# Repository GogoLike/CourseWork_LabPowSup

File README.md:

# CourseWork_LabPowSup
Laboratory Power Supply

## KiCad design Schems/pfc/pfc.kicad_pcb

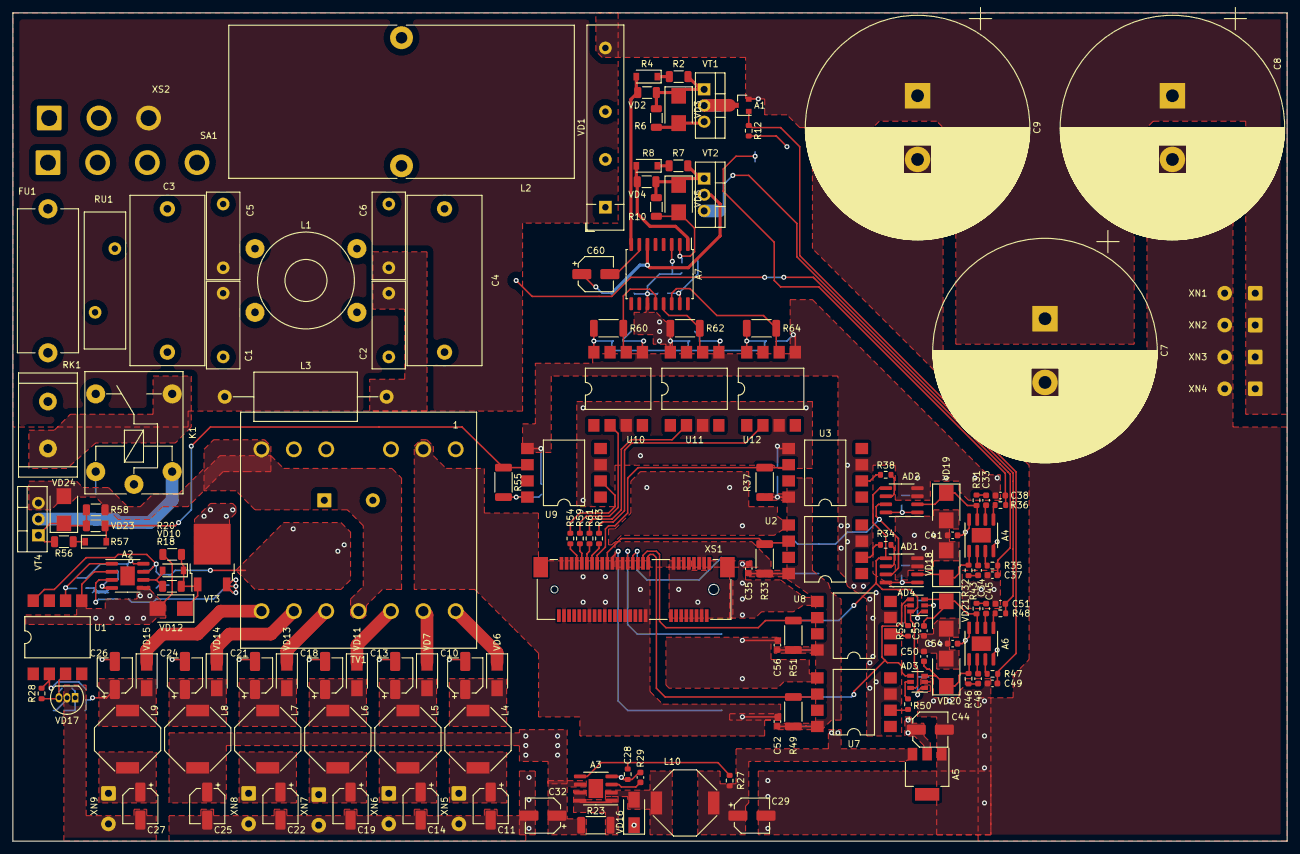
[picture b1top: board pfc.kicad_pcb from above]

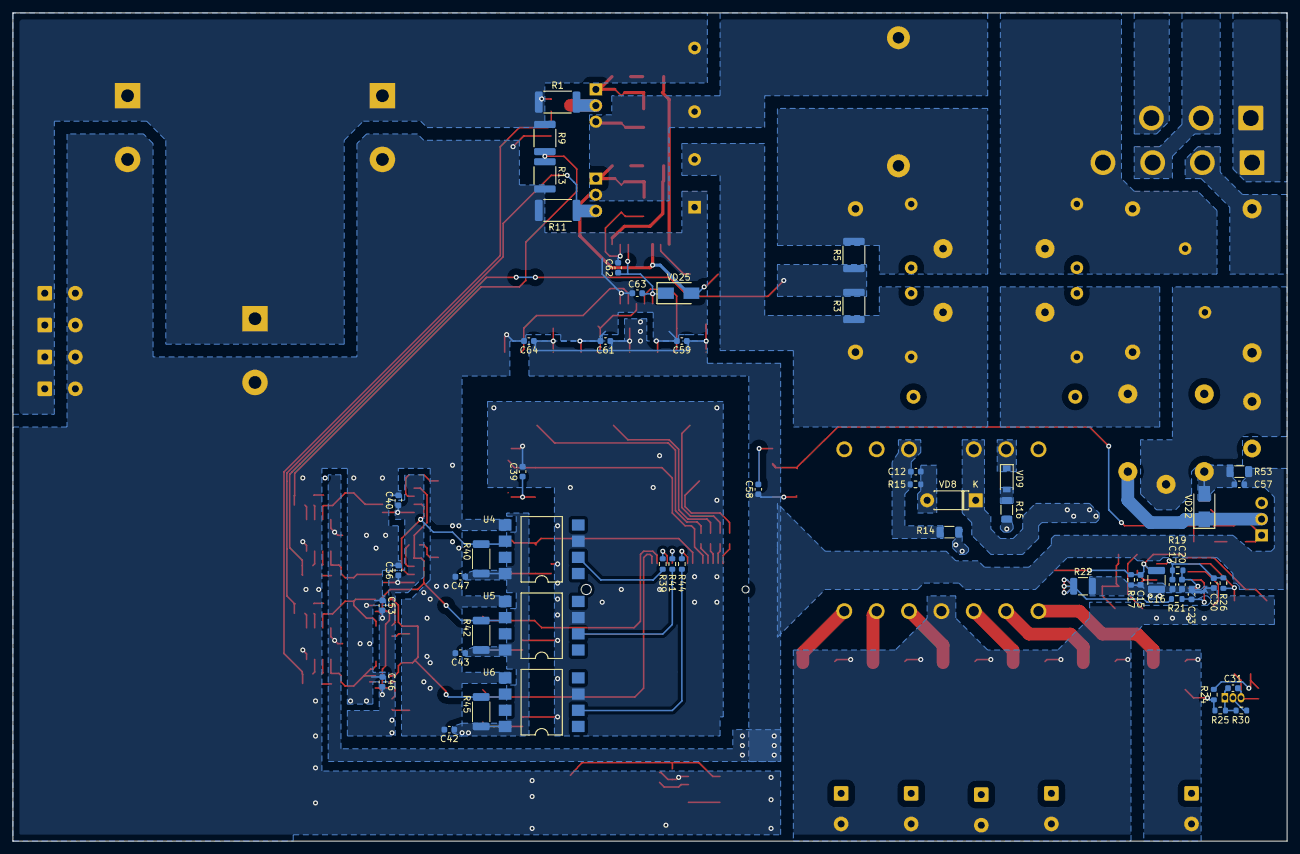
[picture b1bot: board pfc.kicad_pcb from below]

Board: 2 copper layers, 200.0 x 130.0 mm, 207 parts (54 on the bottom side), 118 nets.

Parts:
A1: ZXCT1009F; SOT-23
A2: UC2843; SOIC-8-1EP_3.9x4.9mm_P1.27mm_EP2.29x3mm
A3: MC34063; SOIC-8-1EP_3.9x4.9mm_P1.27mm_EP2.29x3mm
A4, A6: TL103W; SOIC-8-1EP_3.9x4.9mm_P1.27mm_EP2.29x3mm
A5: AMS1117-5; SOT-223
A7: IR2113; SOIC-16W_7.5x10.3mm_P1.27mm
AD1, AD2: MCP3201; SOIC-8_3.9x4.9mm_P1.27mm
AD3, AD4: ADS7886; SOT-23-6
C1, C2, C5, C6: C_CAP; C_Rect_L13.5mm_W5.0mm_P10.00mm_FKS3_FKP3_MKS4
C3, C4: C_CAP; C_Rect_L26.5mm_W11.5mm_P22.50mm_MKS4
C7, C8, C9: 470; CP_Radial_D35.0mm_P10.00mm_SnapIn
C10, C11, C13, C14, C18, C19, C21, C22, C24, C25, C26, C27, C29, C32, C44: 10 25V; CP_Elec_5x5.3
C12: 1.2n; C_0603_1608Metric
C15, C17, C30, C31, C36, C40, C41, C46, C53, C54, C62, C63: 100n; C_0603_1608Metric
C16: 47u; C_1210_3225Metric
C20: 1n; C_0603_1608Metric
C23, C28: 470p; C_0603_1608Metric
C33, C34, C37, C38, C45, C48, C49, C50, C51, C55: C_CAP; C_0603_1608Metric
C35, C39, C42, C43, C47, C52, C56, C58, C59, C61, C64: 15p; C_0603_1608Metric
C57: 1; C_0603_1608Metric
C60: 0.1 25V; CP_Elec_5x5.3
FU1: 20A 250V; Fuseholder_Cylinder-5x20mm_Stelvio-Kontek_PTF78_Horizontal_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
K1: NRP-10-C-12D; Relay_SPDT_Finder_36.11
L1: L_DIEL_DBL_SYN; Transformer_Toroid_Horizontal_D14.0mm_Amidon-T50
L2: L_DIEL; L_Toroid_Vertical_L54.0mm_W23.8mm_P20.10mm_Bourns_5700
L3: L_DIEL; L_Axial_L16.0mm_D7.5mm_P25.40mm_Horizontal_Fastron_XHBCC
L4, L5, L6, L7, L8, L9, L10: 220; L_Bourns-SRU1028_10.0x10.0mm
R1, R11: 0.01 1%; R_2512_6332Metric
R2, R4, R7, R8, R53, R56, R57: R_RES; R_1206_3216Metric
R3, R9: 910k; R_1812_4532Metric
R5, R13: 9.1k; R_1812_4532Metric
R6, R10, R20, R58: 200k; R_1206_3216Metric
R12: 10k 1%; R_0603_1608Metric
R14: 390k; R_1206_3216Metric
R15: 27k; R_0603_1608Metric
R16: 33; R_1206_3216Metric
R17, R25: 15k; R_0603_1608Metric
R18: 22; R_1206_3216Metric
R19: 18k; R_0603_1608Metric
R21, R26, R28: 1k; R_0603_1608Metric
R22: 0.2; R_1210_3225Metric
R23: 0.33; R_2010_5025Metric
R24: 470; R_0603_1608Metric
R27, R29: 4.7k; R_0603_1608Metric
R30: 2k; R_0603_1608Metric
R31, R32, R35, R36, R43, R46, R47, R48: R_RES; R_0603_1608Metric
R33, R37, R40, R42, R45, R49, R51, R55, R60, R62, R64: 100; R_2010_5025Metric
R34, R38, R39, R41, R44, R50, R52, R54, R59, R61, R63: 750; R_0603_1608Metric
RK1: JNR15S221L; R_Radial_Power_L16.1mm_W9.0mm_P7.37mm
RU1: S20K275; RV_Disc_D21.5mm_W6.5mm_P10mm
SA1: 4C 250V 25A; SolderWire-2sqmm_1x04_P7.8mm_D2mm_OD3.9mm
TV1: TV_DIEL_7; Transformer_EPCOS_B66359A1013T_Horizontal
U1, U2, U3, U4, U5, U6, U7, U8: 6N136; SMDIP-8_W11.48mm
U9, U10, U11, U12: 6n136; SMDIP-8_W11.48mm
VD1: KBJ3510; Diode_Bridge_32.0x5.6x17.0mm_P10.0mm_P7.5mm
VD2, VD4, VD23: MBR0540; D_SOD-123
VD3, VD5, VD12, VD24: SMBJ13CA; D_SMB
VD6, VD7, VD11, VD13, VD14, VD15, VD16, VD22, VD25: SK16; D_SMA
VD8: FR107; D_DO-41_SOD81_P7.62mm_Horizontal
VD9, VD10: 1n4148W; D_SOD-123
VD17: TL431; TO-92_Inline
VD18, VD19, VD20, VD21: SMBJ5CA; D_SMB
VT1, VT2: STP34NM60N; TO-220-3_Vertical
VT3: STD3NK80Z; TO-252-2
VT4: VT_NMOS_ENH_GDS; TO-220-3_Vertical
XN1: PWR_OUT0; SolderWire-0.5sqmm_1x02_P4.8mm_D0.9mm_OD2.3mm
XN2: PWR_OUT1; SolderWire-0.5sqmm_1x02_P4.8mm_D0.9mm_OD2.3mm
XN3: PWR_OUT2; SolderWire-0.5sqmm_1x02_P4.8mm_D0.9mm_OD2.3mm
XN4: PWR_OUT3; SolderWire-0.5sqmm_1x02_P4.8mm_D0.9mm_OD2.3mm
XN5: 12V_OUT0; SolderWire-0.5sqmm_1x02_P4.8mm_D0.9mm_OD2.3mm
XN6: 12V_OUT1; SolderWire-0.5sqmm_1x02_P4.8mm_D0.9mm_OD2.3mm
XN7: 12V_OUT2; SolderWire-0.5sqmm_1x02_P4.8mm_D0.9mm_OD2.3mm
XN8: 12V_OUT3; SolderWire-0.5sqmm_1x02_P4.8mm_D0.9mm_OD2.3mm
XN9: 5V_OUT; SolderWire-0.5sqmm_1x02_P4.8mm_D0.9mm_OD2.3mm
XS1: PCIe_mini; BUS_PCI_Express_Mini_Half
XS2: PWR_IN; SolderWire-2sqmm_1x03_P7.8mm_D2mm_OD3.9mm

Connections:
0: C26.2, C27.2, C35.2, C39.2, C52.2, C56.2, R30.2, TV1.2, U2.5, U3.5, U4.3, U5.3, U6.3, U7.5, U8.5, U9.3, U10.3, U11.3, U12.3, VD17.2, XN9.2, XS1.4, XS1.9, XS1.15, XS1.18, XS1.21, XS1.26, XS1.27, XS1.29, XS1.34, XS1.35, XS1.40, XS1.50
+5V: C27.1, C35.1, C39.1, C52.1, C56.1, L9.2, R33.2, R37.2, R49.2, R51.2, U2.8, U3.8, U7.8, U8.8, XN9.1, XS1.3, XS1.5
+6V: A5.3, C29.1, C42.1, C43.1, C47.1, L10.2, R27.1, R40.2, R42.2, R45.2, U4.8, U5.8, U6.8
+12V: A3.6, A4.8, A6.8, A7.3, A7.11, C25.1, C32.1, C41.1, C54.1, C57.1, C58.1, C59.1, C61.1, C62.1, C63.2, C64.1, L8.2, R23.2, R53.1, R55.2, R60.2, R62.2, R64.2, U9.8, U10.8, U11.8, U12.8, VD25.1
+400V: A1.2, C7.1, C8.1, C9.1, C12.1, R1.1, R9.1, R14.1, R15.1, TV1.3, VD1.1, XN1.1, XN2.1, XN3.1, XN4.1
-400V: A2.2, A2.5, A3.4, A4.4, A5.1, A6.4, A7.2, A7.15, AD1.3, AD1.4, AD2.3, AD2.4, AD3.2, AD4.2, C7.2, C8.2, C9.2, C10.2, C11.2, C13.2, C14.2, C15.2, C16.2, C17.2, C18.2, C19.2, C20.2, C21.2, C22.2, C23.2, C24.2, C25.2, C28.2, C29.2, C30.2, C32.2, C36.2, C37.1, C38.2, C40.2, C41.2, C42.2, C43.2, C44.2, C46.1, C47.2, C49.1, C50.2, C51.2, C53.1, C54.2, C55.2, C58.2, C59.2, C61.2, C62.2, C63.1, C64.2, R10.2, R11.2, R12.2, R13.2, R17.2, R20.2, R22.2, R29.2, R58.2, TV1.7, TV1.11, U1.5, U2.3, U3.3, U4.5, U5.5, U6.5, U7.3, U8.3, U9.5, U10.5, U11.5, U12.5, VD1.4, VD5.2, VD12.2, VD16.1, VD18.2, VD19.2, VD20.2, VD21.2, VD24.2, VT4.3, XN1.2, XN2.2, XN3.2, XN4.2, XN5.2, XN6.2, XN7.2, XN8.2
CLK: R39.1, XS1.23
GND: C1.2, C5.1, L3.1, XS2.3
HI: R59.1, XS1.43
HO: A7.8, R4.1, VD2.2
HS: A7.6, C60.1, L2.2, R6.2, VD1.3, VD3.2, VD25.2, VT1.3, VT2.2
IdwD: R51.1, U8.6, XS1.19
IdwS: C51.1, R11.1, R48.2, VT2.3
IupD: R49.1, U7.6, XS1.17
IupS: A1.1, C49.2, R12.1, R47.2
LI: R63.1, XS1.39
LO: A7.1, R8.1, VD4.2
unnamed: A1.3, R1.2, VT1.2
unnamed: A2.1, R26.2, U1.6
unnamed: A2.3, C23.1, R21.1
unnamed: A2.4, C20.1, R19.2
unnamed: A2.6, R18.1, VD10.2
unnamed: A2.7, C15.1, C16.1, R14.2, R16.1, R17.1, U1.8
unnamed: A2.8, C17.1, C30.1, R19.1, R26.1
unnamed: A3.1, A3.7, A3.8, R23.1
unnamed: A3.2, L10.1, VD16.2
unnamed: A3.3, C28.1
unnamed: A3.5, R27.2, R29.1
unnamed: A4.1, AD1.2, R32.1, VD18.1
unnamed: A4.2, C34.2
unnamed: A4.3, R35.1
unnamed: A4.5, R36.1
unnamed: A4.6, C33.2
unnamed: A4.7, AD2.2, R31.1, VD19.1
unnamed: A5.2, AD1.1, AD1.8, AD2.1, AD2.8, AD3.1, AD4.1, C36.1, C40.1, C44.1, C46.2, C53.2
unnamed: A6.1, AD3.3, C50.1, R46.1, VD20.1
unnamed: A6.2, C48.2
unnamed: A6.3, R47.1
unnamed: A6.5, R48.1
unnamed: A6.6, C45.2
unnamed: A6.7, AD4.3, C55.1, R43.1, VD21.1
unnamed: A7.7, C60.2
unnamed: A7.12, R60.1, U10.6
unnamed: A7.13, R62.1, U11.6
unnamed: A7.14, R64.1, U12.6
unnamed: AD1.5, AD2.5, AD3.6, AD4.6, R42.1, U5.6
unnamed: AD1.6, R34.1
unnamed: AD1.7, AD2.7, R40.1, U4.6
unnamed: AD2.6, R38.1
unnamed: AD3.4, AD4.4, R45.1, U6.6
unnamed: AD3.5, R50.1
unnamed: AD4.5, R52.1
unnamed: C1.1, C3.1, K1.5, L1.1, RK1.2
unnamed: C2.1, C4.1, L1.2, R3.1, VD1.2
unnamed: C2.2, C6.1, L3.2
unnamed: C3.2, C5.2, L1.3, RU1.1, SA1.4
unnamed: C4.2, C6.2, L1.4, L2.1, R5.2
unnamed: C10.1, L4.1, VD6.2
unnamed: C11.1, L4.2, XN5.1
unnamed: C12.2, R15.2, VD8.2
unnamed: C13.1, L5.1, VD7.2
unnamed: C14.1, L5.2, XN6.1
unnamed: C18.1, L6.1, VD11.2
unnamed: C19.1, L6.2, XN7.1
unnamed: C21.1, L7.1, VD13.2
unnamed: C22.1, L7.2, XN8.1
unnamed: C24.1, L8.1, VD14.2
unnamed: C26.1, L9.1, R24.1, R25.1, VD15.2
unnamed: C31.1, R28.2, U1.3, VD17.3
unnamed: C31.2, R25.2, R30.1, VD17.1
unnamed: C33.1, R31.2
unnamed: C34.1, R32.2
unnamed: C45.1, R43.2
unnamed: C48.1, R46.2
unnamed: FU1.1, SA1.2
unnamed: FU1.2, K1.4, RK1.1, RU1.2
unnamed: R2.1, VD2.1
unnamed: R2.2, R4.2, R6.1, VD3.1, VT1.1
unnamed: R7.1, VD4.1
unnamed: R7.2, R8.2, R10.1, VD5.1, VT2.1
unnamed: R16.2, VD9.2
unnamed: R18.2, R20.1, VD10.1, VD12.1, VT3.1
unnamed: R21.2, R22.1, VT3.3
unnamed: R24.2, R28.1, U1.2
unnamed: R34.2, U2.2
unnamed: R38.2, U3.2
unnamed: R39.2, U4.2
unnamed: R41.2, U5.2
unnamed: R44.2, U6.2
unnamed: R50.2, U7.2
unnamed: R52.2, U8.2
unnamed: R54.2, U9.2
unnamed: R55.1, R57.1, U9.6, VD23.2
unnamed: R56.1, VD23.1
unnamed: R56.2, R57.2, R58.1, VD24.1, VT4.1
unnamed: R59.2, U10.2
unnamed: R61.2, U11.2
unnamed: R63.2, U12.2
unnamed: SA1.1, XS2.1
unnamed: SA1.3, XS2.2
unnamed: TV1.5, VD8.1, VT3.2
unnamed: TV1.6, VD9.1
unnamed: TV1.8, VD15.1
unnamed: TV1.9, VD14.1
unnamed: TV1.10, VD13.1
unnamed: TV1.12, VD11.1
unnamed: TV1.13, VD7.1
unnamed: TV1.14, VD6.1
Relay: R54.1, XS1.45
RelayCtrl+: C57.2, K1.2, R53.2, VD22.2
RelayCtrl-: K1.1, VD22.1, VT4.2
SCLK: R44.1, XS1.31
SD: R61.1, XS1.41
UinD: R33.1, U2.6, XS1.33
UinS: C37.2, R3.2, R5.1, R35.2
UoutD: R37.1, U3.6, XS1.37
UoutS: C38.1, R9.2, R13.1, R36.2
~CS: R41.1, XS1.25

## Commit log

2021-10-31 Adding all files
    Добавил файлы, лежащие локально на ноутбуке.
2021-10-31 Edit .gitignore and edit Полумост.cir
2021-10-31 Add Объединение обмоток
2021-11-21 Начал расчёт обратноходовой дежурки
2021-12-04 Добавил книги
2021-12-04 Сложил книги в папку
2021-12-04 Переложил рпз. Отредактировал gitignore под файлы микрокапа.
2021-12-04 Тщетные попытки заставить обратноходовик работать.
2021-12-15 Добавил книги по микрокапу от Загидуллина
2022-02-03 Много изменений
2022-03-05 Дежурное питание заново
2022-03-05 Сделал идеальный трансформатор на нужное количество портов
    Исследовал разные трансформаторы в простейшей схеме.
    Пришёл к выводу, что хватит и идеального.
    Сделал необходимый идеальный из макромодели.
    Начал проектирование блока с микросхемой.
2022-03-13 Закончил расчёт дежурного питания
    Изменил времязадающую цепь, поменял номинал подстроечного резистора TL431.
2022-04-22 All Course_Work done
